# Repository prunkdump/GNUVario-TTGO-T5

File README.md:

# Gnuvario_for_TTGO-T5
# GNUVARIO-E     Stable version ---
# GNUVARIO-E     Developpement version 0.6 beta 7
# PCB            version 2.1
# 3D CASE        version 2.01

 v 0.1                              beta 1 version                     
 v 0.2     beta 1      23/06/19     debug VarioScreen                        
 v 0.3     beta 1      25/06/19     correction mesure tension          
                                    correction mesure de vitesse       
 v 0.3     beta 2      26/06/19     correction save IGC                                                 
 v 0.4     beta 1      03/07/19     ajout la coupure du son            
 v 0.4     beta 2      06/07/19     ajout statistique                  
 v 0.4     beta 3      18/07/19     Correction gestion Eeprom          
                                    Correction tache affichage          
                                    Ajout delete task display          
                                    Correction affichage statistique   
 v 0.4      beta 4      22/07/19    Correction effacement screendigit                               
                                    Correction affichage duree du vol  
                                    Correction affichage statistique   
                                    Modification FlightHistory         
                                    Ajout parametre flighthistory dans 
                                    SETTINGS.TXT                       
                                    Enregistrement des statistique     
                                    toutes les 60sec - reduction des   
                                    cycle d'ecriture dans la mémoire   
                                    flash de l'ESP32                   
 v 0.4     beta 5    24/07/19       Ajout TrendDigit                   
                                    Modification TrendLevel            
                                    Modification screendigit           
                                    Correction démarrage du vol    
 v 0.4     beta 6    25/07/19       Ajout NO_RECORD                                                                                          
                                    Correction TWOWIRESCHEDULER        																		
 
 v 0.4     beta 7    05/08/19       Désactivation enregistrement stat  
                                    pour eviter le bug du plantage      
                                    Ajout paramettre wifi              
                                    Modification SETTINGS.TXT v1.2     
 v 0.4     beta 8    06/08/19       Ajout icone Norecord               
                                    Correction bug statistique         
                                    Raffraichissement de l'ensemle de  
                                    l'écran toutes les 30sec           
 v 0.5     beta 1    10/08/19       Ajout Gestionnaire d'erreur ESP32  
                                    Mise à jour via SDCARD /update.bin 
                                    Ajout Serveur Web update/download  
                                    Ajout HAVE_WIFI                    
                                    Ajout BT                           
 v 0.5     beta 2    20/08/19       Ajout dans hardwareConfig32 de la  
                                    version du PCB et de la TTGO       
                                    Ajout lecture de la temperature    
                                    MAJ OTA Web serveur                
                                    Ajout changement de page           
                                    Ajout 2ème ecran                   

 v 0.5     beta 3  25/08/19         Ajout LOW/HIGH level cmd ampli     
                                    Ajout ecran reglage volume du son  
                                    Correction Bug bouton              

 v 0.5     beta 4  30/08/19         Ajout écran stat 
                                    Modification librairie ToneHAL 
																		Correction bug d'affichage mineurs

 v 0.5     beta 5  31/08/19         Correction bg reglage volume       
                                    Ajout commande ampli dans loop     
                                    pour test                          
 
 v 0.5     beta 6  04/09/19         Changement librairies MS5611 et MPU9250                                                             
                                    Modification de la calibration de l'altitude par le GPS                  
                                    Ajout d'un coeficiant de compensation de temperature             
                                    Modification de la séquence de démarrage de l'enregistrement   
																		
 v 0.5     beta 7  10/09/19         Ajout choix des pin SDA, SCL                                                                                                       
                                    Modification des librairies du MPU9250 / ajout fonctions de                                                                                   
                                    Calibration                                                      
                                    Ajout Son de monté variable                                      
                                    Modification de la sequence de démarrage -                       
                                    allongement du temps de l'écran de stat à 6 sec                  
                                    init MS5611 avant ecran stat, ajout acquisition durant ecran     
                                    stat et init kalman après                                        
                                    Ajout d'un paramettre de nombre d'acquisition du GPS avant        
                                    la mise à jour de Altitude Barometrique                          
                                    Modification librairie EEPROM                                    
																		
                   Developpement à venir                               
                                                                                                                                    
 V0.4                                                                                                                                          																												
 bug affichage finesse  
 
 V0.5                                                                  
 voir réactivité des données GPS                                                                     
 Probleme consommasion - SDcard - deep slepp                                                         
                                                                                                     
 v0.6                                                                                                   
 MODIF - Refaire gestion Eeprom avec preference                                                      
 AJOUT - Calibration MPU                                                                                                              
 AJOUT - gestion du MPU par Interruption                                                             
 BUG   - reboot à l'init du MPU  - nan lors du first alti                                            
 BUG   - blocage MPU - plus de valeur valide                                                         
 BUG   - temperature                                                                                 
 BUG   - DISPLAY_OBJECT_LINE object ligne ne fonctionne pas                                          
 AJOUT - Créer une bibliothèque de log (debug)  avec fichier de log                                  
 BUG   - Alti erreur deep sleep non validé                                                               
 BUG   - Norcissement de l'écran                                                                     
                                                                                                     
 VX.X                                                                                                
 Paramètrage des écrans                                                                             
 Gérer le son via le DAC                                                                             
 revoir volume du son ToneESP32                                                                      
 Refaire gestion du son (parametrage via xctracer)                                                   
 Ecran position afficher les coordonées GPS, la boussole, et l'altitude                                                                                                     
 Création dynamique des objets screen                                                                
 Sens et vitesse du vent                                                                             
 Carnet de vol (10 derniers vols)                                                                    
 verifier fonctionnement BT                                                                          
 Recupération vol via USB                                                                                                                                                                    
 Ecran 2.9'' en vertical                                                                             

                    Fonctionalitées   
		
  Version 0		
    Vario précis avec capteur de pression et accéleromètres
    GPS
    Enregistrement des vols sur carte SD
    Affichage sur ecran E-Ink
    Affichage du vario, de l'altitude, de la vitesse sol,
    de l'heure, du temps de vol, ...
                                                                       
  Version 0.3                                                                                                                               
    Parametre utilisateur dans fichier SETTINGS.TXT                    
    Coupure du son via le bouton central (en vol)                      
                                                                       
  Version 0.4                                                          
    Statistiques de Vol                                                
    taux de chute et finesse                                           
    indicateur de monte/descente 
    Désactiver l'enregistrement des vols		
                                                                       
  Version 0.5                                                            
    Mise à jour via la carte SD (update.bin)                            
    Récupération des vol via Wifi                                         
    Mise à jour via Wifi                                                  
    Upload des fichiers de configuration via Wifi                         
    Ajout Bluetooth                                                       
    Multi-écran (ajout 2ème page / gestion des bouton droit et gauche)    
    Affichage de la température        
		Page de configuration du volume sonore   
    Page de statistique accessible via les boutons    	
		Mise en veille automatique en cas de batterie trop faible               
                                                                              
  Version 0.6                                                              
    Page de calibration                                                      
    Mise en veille prolongée par bouton                                                  
    Ajout gestion des écran 2.9'' et 2.13''                                  
    Ajout du serveur Web sur SDCARD                                          
    Activation du Bluetooth en parametre dans le fichier de configuration       
    Ajout de titre au dessus des champs de données                          
    Ajout de nouveau objects screen - ligne - rose des vents                
    Modification de l'organisation des fichiers sur la carte SD                
    Ajout compensation de température         
    Ajout correction d'altitude GPS                     
    Modification calibration alti GPS - 5 mesures puis moyenne de l'altitude sur 10 mesures avant de calibrer le barometre                   
    3 fichiers de paramètrage params.jso, wifi.cfg, variocal.cfg               
    Gestion automatique de la mise à jour du fichier params.jso en cas d'ajout ou de suppréssion de champs                                       
    Mise en veille en cas d'inactivité, paramètrable - 0 infini

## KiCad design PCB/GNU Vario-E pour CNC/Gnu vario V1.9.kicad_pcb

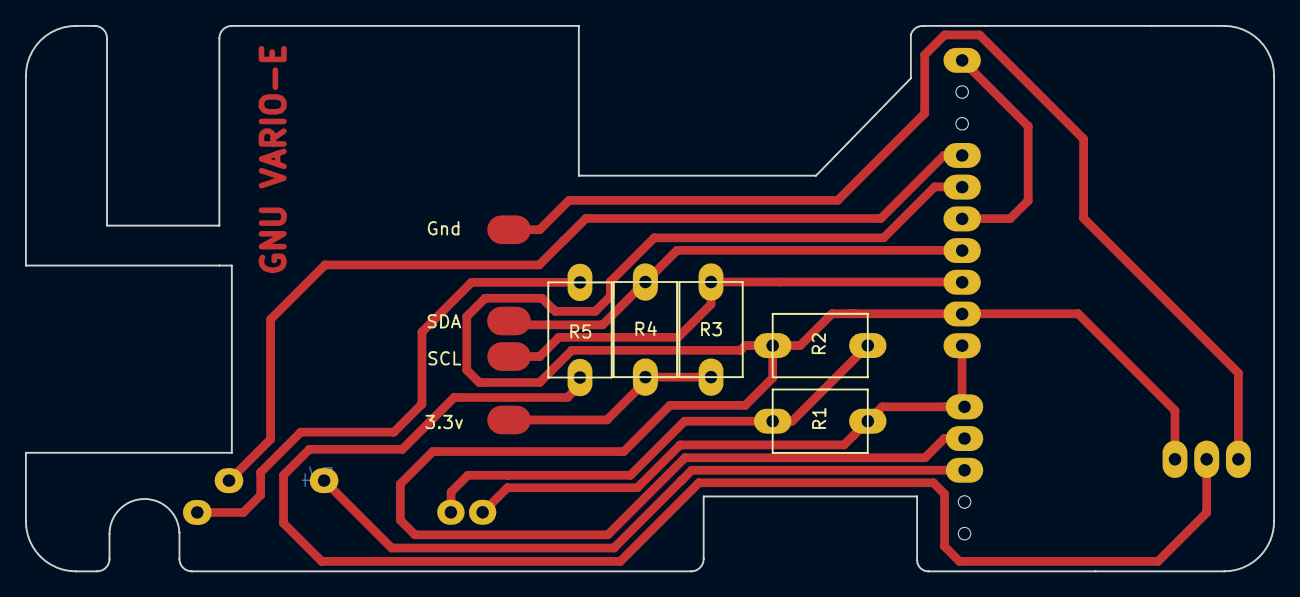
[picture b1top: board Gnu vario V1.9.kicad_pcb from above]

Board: 2 copper layers, 100.0 x 43.7 mm, 10 parts (0 on the bottom side), 12 nets.

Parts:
BCxxx1: S8050; Transistor
J1: Conn_01x05; Pads_connection
R1: 270k; R1
R2: 1M; R1
R3, R4: 4.7k; R1
R5: 1K; R1
TTGO T5 V1.x: TTGO_T5; TTGO_T5_V1.09
U1: CJMCU_117; CJMCU-117
U2: ATGM336H; GPS

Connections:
unnamed: BCxxx1.1, J1.1
unnamed: BCxxx1.2, R5.2
unnamed: BCxxx1.3, R2.1, U1.2, U1.6, U2.2
unnamed: R1.2, TTGO T5 V1.x.3, U1.1, U2.1
unnamed: R1.1, R2.2, TTGO T5 V1.x.4
unnamed: R5.1, TTGO T5 V1.x.12
unnamed: TTGO T5 V1.x.20, U2.3
unnamed: TTGO T5 V1.x.23, U1.7
unnamed: J1.3, R4.1, U1.4
unnamed: J1.4, R3.1, U1.3
unnamed: J1.5, R3.2, R4.2
unnamed: U1.5, U1.10

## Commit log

2019-08-20 Added readme
2019-09-19 SOURCE BETA - 0.5 Beta 7 PCB - V 2.1
2019-09-20 SOURCE BETA - Version 0.5 Beta 7
2019-09-20 Ajout Photos
2019-09-26 Ajout fiche de présentation
2019-09-27 BOITIER 3D - Version 1.06 / ajout capuchon slide switch
2019-10-18 PCB - Mise à jour PCB V2.1
2019-10-18 SOURCE BETA - version 0.5 Beta 6 - testée sur PCBv2
2019-10-18 MAJ Readme
2019-10-23 BOITIER 3D - Version 2.00
2019-10-23 PCB - Version 2
2019-11-04 Ajout RootSD, Calibration
2019-11-05 BOITIER 3D - Ajout Photos
2019-11-12 BOITIER 3D - Maj 1.52'' V2.01
2019-11-28 SOURCE BETA - version 0.6 Beta 7
2019-11-30 BOITIER 3D - Ajout 2.9''
2019-12-08 Maj capuchon
2019-12-24 SOURCE BETA - version 0.7 Beta 3
2020-01-09 SOURCE BETA - version 0.7 Beta 5
2020-01-11 SOURCE BETA - version 0.7 Beta 6
2020-01-13 SOURCE BETA - Sdcard V0.7 beta 6
2020-03-14 SOURCE BETA - version 0.7 beta 8 BOITIER 3D - version 2.01 - Boitier 2.9'' portrait
2020-05-14 SOURCE BETA - version 0.8 beta 1
2020-05-24 SOURCE BETA - version 0.8 beta 2
2020-06-23 SOURCE BETA - version 0.8 beta 3
2020-07-24 Test materiel
2020-09-27 Test librairie varioXBeeper
2020-10-17 SOURCE BETA - version 0.8 beta 4
2020-10-18 SOURCE BETA - version 0.8 beta 4 - vscode
2020-12-13 SOURCE BETA - version 0.8 beta 5
2020-12-20 SOURCE BETA - version 0.8 beta 5 - MAJ RootSD
2020-12-21 SOURCE BETA - version 0.8 beta 5 - Corrections
2021-02-10 SOURCE BETA - version 0.8 beta 5 - Maj ecran V2
2021-04-19 Boitier 3D - version 2.05
    correction sur le boitier 1.54'' et 2.9'' portrait
2021-06-12 SOURCE BETA - version 0.8 beta 6
2021-06-27 SOURCE BETA - version 0.8 beta 6 - Correction CAP + quelques bugs
2021-06-27 BINAIRE - version 0.8 beta 6
2021-06-29 ROOTSD - version 0.8 beta 6
